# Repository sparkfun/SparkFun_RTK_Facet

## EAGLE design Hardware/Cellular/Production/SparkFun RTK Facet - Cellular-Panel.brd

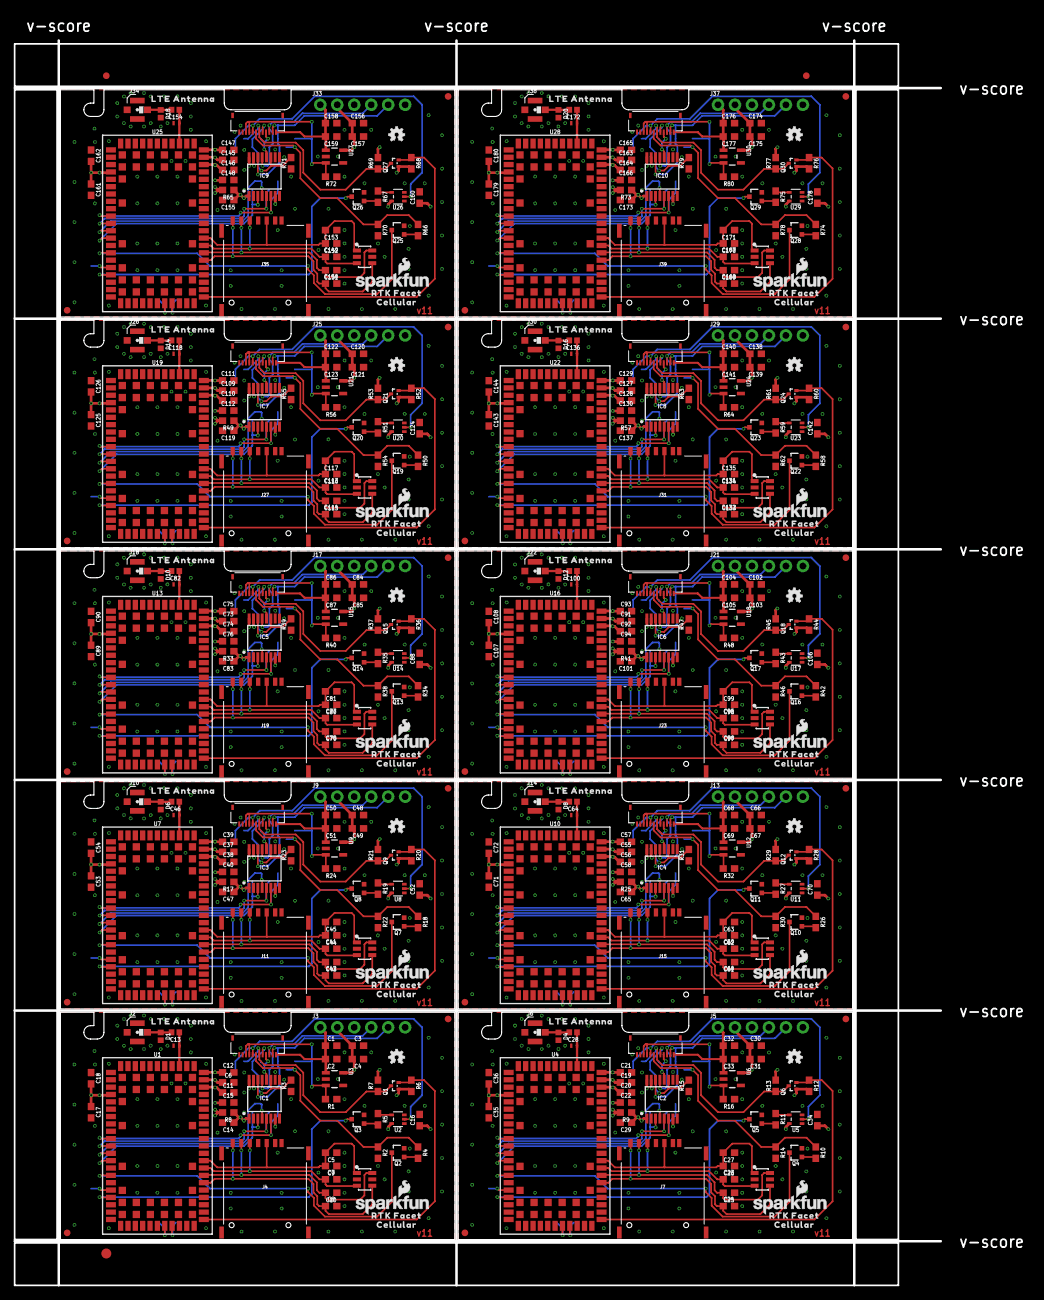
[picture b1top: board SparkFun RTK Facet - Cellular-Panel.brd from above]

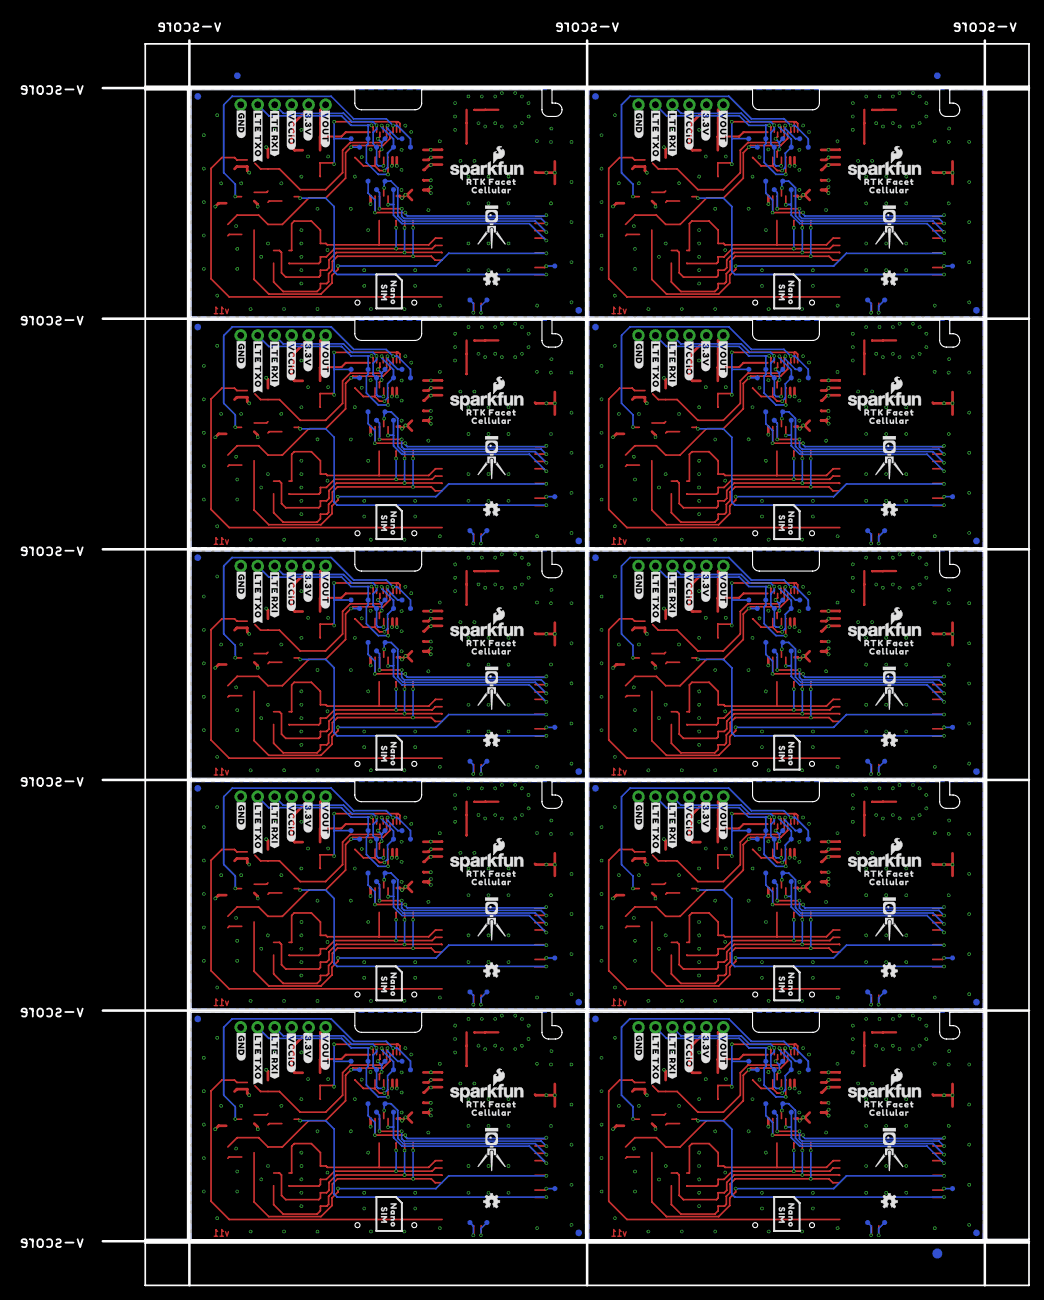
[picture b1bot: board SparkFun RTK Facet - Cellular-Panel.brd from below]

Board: 4 copper layers, 138.6 x 186.3 mm, 776 parts (303 on the bottom side), 320 nets.

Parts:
C1, C3, C17, C30, C32, C35, C48, C50, C53, C66, C68, C71, C84, C86, C89, C102, C104, C107, C120, C122, C125, C138, C140, C143, C156, C158, C161, C174, C176, C179: 1.0uF; 0603
C2, C4, C5, C6, C14, C16, C18, C19, C27, C29, C31, C33, C34, C36, C37, C45, C47, C49, C51, C52, C54, C55, C63, C65, C67, C69, C70, C72, C73, C81, C83, C85, C87, C88, C90, C91, C99, C101, C103, C105, C106, C108, C109, C117, C119, C121, C123, C124, C126, C127, C135, C137, C139, C141, C142, C144, C145, C153, C155, C157, C159, C160, C162, C163, C171, C173, C175, C177, C178, C180: 0.1uF; 0603
C7, C8, C9, C10, C23, C24, C25, C26, C41, C42, C43, C44, C59, C60, C61, C62, C77, C78, C79, C80, C95, C96, C97, C98, C113, C114, C115, C116, C131, C132, C133, C134, C149, C150, C151, C152, C167, C168, C169, C170: 47pF; 0603
C11, C20, C38, C56, C74, C92, C110, C128, C146, C164: 68pF; 0603
C12, C21, C39, C57, C75, C93, C111, C129, C147, C165: 10uF; 0603
C13, C28, C46, C64, C82, C100, C118, C136, C154, C172: 33pF; 0402
C15, C22, C40, C58, C76, C94, C112, C130, C148, C166: 15pF; 0603
D1, D4, D6, D8, D10, D12, D14, D16, D18, D20: PESD0402; 0402
D2, D3, D5, D7, D9, D11, D13, D15, D17, D19: DT1042-04SO-7; SOT23-6L
E$1, E$2, E$3, E$4: FIDUCIAL-1X2
E$5, E$6: FIDUCIAL-1.5X3
FID1, FID2, FID3, FID4, FID5, FID6, FID7, FID8, FID9, FID10, FID11, FID12, FID13, FID14, FID15, FID16, FID17, FID18, FID19, FID20, FID21, FID22, FID23, FID24, FID25, FID26, FID27, FID28, FID29, FID30, FID31, FID32, FID33, FID34, FID35, FID36, FID37, FID38, FID39, FID40: FIDUCIAL1X2; FIDUCIAL-1X2
IC1, IC2, IC3, IC4, IC5, IC6, IC7, IC8, IC9, IC10: SN74AVC4T774PW; SOP65P640X120-16N
J1, J8, J12, J16, J20, J24, J28, J32, J36, J40: FPC_12_DOUBLESIDED_BACKFLIP
J2, J6, J10, J14, J18, J22, J26, J30, J34, J38: U.FL
J3, J5, J9, J13, J17, J21, J25, J29, J33, J37: DIAG; 1X06_NO_SILK
J4, J7, J11, J15, J19, J23, J27, J31, J35, J39: NANO_SIM_PP_REDUCED_PADS
L1, L2, L3, L4, L5, L6, L7, L8, L9, L10: DNP; 0402_COILCRAFT
LOGO1, LOGO3, LOGO4, LOGO8, LOGO9, LOGO12, LOGO13, LOGO16, LOGO17, LOGO20, LOGO21, LOGO24, LOGO25, LOGO28, LOGO29, LOGO32, LOGO33, LOGO36, LOGO37, LOGO40: OSHW-LOGOMINI; OSHW-LOGO-MINI
LOGO2, LOGO5, LOGO6, LOGO7, LOGO10, LOGO11, LOGO14, LOGO15, LOGO18, LOGO19, LOGO22, LOGO23, LOGO26, LOGO27, LOGO30, LOGO31, LOGO34, LOGO35, LOGO38, LOGO39: SFE_LOGO_NAME_FLAME.1_INCH; SFE_LOGO_NAME_FLAME_.1
Q1, Q6, Q9, Q12, Q15, Q18, Q21, Q24, Q27, Q30: 20V/0.2A/8MHz/1.2Ω/1Vth; SOT-416FL
Q2, Q3, Q4, Q5, Q7, Q8, Q10, Q11, Q13, Q14, Q16, Q17, Q19, Q20, Q22, Q23, Q25, Q26, Q28, Q29: 310mA/60V/1.6Ω; SOT323
R1, R2, R3, R14, R15, R16, R22, R23, R24, R30, R31, R32, R38, R39, R40, R46, R47, R48, R54, R55, R56, R62, R63, R64, R70, R71, R72, R78, R79, R80: 100k; 0603
R4, R5, R10, R11, R18, R19, R26, R27, R34, R35, R42, R43, R50, R51, R58, R59, R66, R67, R74, R75: 1k; 0603
R6, R7, R12, R13, R20, R21, R28, R29, R36, R37, R44, R45, R52, R53, R60, R61, R68, R69, R76, R77: 2.2k; 0603
R8, R9, R17, R25, R33, R41, R49, R57, R65, R73: 0; 0603
TP1, TP2, TP3, TP4, TP5, TP6, TP7, TP8, TP9, TP10, TP11, TP12, TP13, TP14, TP15, TP16, TP17, TP18, TP19, TP20, TP21, TP22, TP23, TP24, TP25, TP26, TP27, TP28, TP29, TP30, TP31, TP32, TP33, TP34, TP35, TP36, TP37, TP38, TP39, TP40, TP41, TP42, TP43, TP44, TP45, TP46, TP47, TP48, TP49, TP50, TP51, TP52, TP53, TP54, TP55, TP56, TP57, TP58, TP59, TP60, TP61, TP62, TP63, TP64, TP65, TP66, TP67, TP68, TP69, TP70, TP71, TP72, TP73, TP74, TP75, TP76, TP77, TP78, TP79, TP80, TP81, TP82, TP83, TP84, TP85, TP86, TP87, TP88, TP89, TP90, TP91, TP92, TP93, TP94, TP95, TP96, TP97, TP98, TP99, TP100, TP101, TP102, TP103, TP104, TP105, TP106, TP107, TP108, TP109, TP110, TP111, TP112, TP113, TP114, TP115, TP116, TP117, TP118, TP119, TP120, TP121, TP122, TP123, TP124, TP125, TP126, TP127, TP128, TP129, TP130, TP131, TP132, TP133, TP134, TP135, TP136, TP137, TP138, TP139, TP140, TP141, TP142, TP143, TP144, TP145, TP146, TP147, TP148, TP149, TP150: TEST-POINT3; PAD.03X.03
U1, U4, U7, U10, U13, U16, U19, U22, U25, U28: SARA-R510M8S; SARA-LGA
U2, U5, U8, U11, U14, U17, U20, U23, U26, U29: 74HC1G04; SOT353
U3, U6, U9, U12, U15, U18, U21, U24, U27, U30: AP2112K-3.3; SOT23-5
U$1, U$12, U$14, U$17, U$28, U$31, U$42, U$45, U$56, U$59, U$70, U$73, U$84, U$87, U$98, U$101, U$112, U$115, U$126, U$129: RTK_FACET0
U$2, U$3, U$11, U$18, U$27, U$32, U$41, U$46, U$55, U$60, U$69, U$74, U$83, U$88, U$97, U$102, U$111, U$116, U$125, U$132: CELLULAR1
U$4, U$19, U$33, U$47, U$61, U$75, U$89, U$103, U$117, U$133: #VOUT#0
U$5, U$20, U$34, U$48, U$62, U$76, U$90, U$104, U$118, U$134: #3#3V#0
U$6, U$21, U$35, U$49, U$63, U$77, U$91, U$105, U$119, U$135: #VCCIO#0
U$7, U$22, U$36, U$50, U$64, U$78, U$92, U$106, U$120, U$136: #LTE_RXI#0
U$8, U$23, U$37, U$51, U$65, U$79, U$93, U$107, U$121, U$137: #LTE_TXO#0
U$9, U$24, U$38, U$52, U$66, U$80, U$94, U$108, U$122, U$138: #GND#0
U$10, U$26, U$40, U$54, U$68, U$82, U$96, U$110, U$124, U$140: LTE_ANTENNA0
U$13, U$29, U$43, U$57, U$71, U$85, U$99, U$113, U$127, U$130: NANO0
U$15, U$25, U$39, U$53, U$67, U$81, U$95, U$109, U$123, U$139: RTK5#SVG0
U$16, U$30, U$44, U$58, U$72, U$86, U$100, U$114, U$128, U$131: SIM0

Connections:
3.3V: C3.1, C4.2, C6.1, C11.1, C12.1, C15.1, C16.1, IC1.15, J3.2, R7.2, U1.51, U1.52, U1.53, U2.5, U3.5
3.3V1: C19.1, C20.1, C21.1, C22.1, C30.1, C31.2, C34.1, IC2.15, J5.2, R13.2, U4.51, U4.52, U4.53, U5.5, U6.5
3.3V2: C37.1, C38.1, C39.1, C40.1, C48.1, C49.2, C52.1, IC3.15, J9.2, R21.2, U7.51, U7.52, U7.53, U8.5, U9.5
3.3V3: C55.1, C56.1, C57.1, C58.1, C66.1, C67.2, C70.1, IC4.15, J13.2, R29.2, U10.51, U10.52, U10.53, U11.5, U12.5
3.3V4: C73.1, C74.1, C75.1, C76.1, C84.1, C85.2, C88.1, IC5.15, J17.2, R37.2, U13.51, U13.52, U13.53, U14.5, U15.5
3.3V5: C91.1, C92.1, C93.1, C94.1, C102.1, C103.2, C106.1, IC6.15, J21.2, R45.2, U16.51, U16.52, U16.53, U17.5, U18.5
3.3V6: C109.1, C110.1, C111.1, C112.1, C120.1, C121.2, C124.1, IC7.15, J25.2, R53.2, U19.51, U19.52, U19.53, U20.5, U21.5
3.3V7: C127.1, C128.1, C129.1, C130.1, C138.1, C139.2, C142.1, IC8.15, J29.2, R61.2, U22.51, U22.52, U22.53, U23.5, U24.5
3.3V8: C145.1, C146.1, C147.1, C148.1, C156.1, C157.2, C160.1, IC9.15, J33.2, R69.2, U25.51, U25.52, U25.53, U26.5, U27.5
3.3V9: C163.1, C164.1, C165.1, C166.1, C174.1, C175.2, C178.1, IC10.15, J37.2, R77.2, U28.51, U28.52, U28.53, U29.5, U30.5
GND: C1.2, C2.1, C3.2, C4.1, C5.1, C6.2, C7.2, C8.2, C9.1, C10.1, C11.2, C12.2, C14.2, C15.2, C16.2, C17.2, C18.1, D1.2, D2.2, D2.5, IC1.2, IC1.8, IC1.9, IC1.10, J1.11, J1.12, J2.1, J2.2, J3.6, J4.C5, L1.P$2, Q2.2, Q3.2, R1.1, R2.2, R3.1, U1.1, U1.3, U1.5, U1.9, U1.14, U1.20, U1.21, U1.22, U1.30, U1.32, U1.43, U1.50, U1.54, U1.55, U1.57, U1.58, U1.59, U1.60, U1.61, U1.63, U1.64, U1.65, U1.66, U1.67, U1.68, U1.69, U1.70, U1.71, U1.72, U1.73, U1.74, U1.75, U1.76, U1.77, U1.78, U1.79, U1.80, U1.81, U1.82, U1.83, U1.84, U1.85, U1.86, U1.87, U1.88, U1.89, U1.90, U1.91, U1.92, U1.93, U1.94, U1.95, U1.96, U2.3, U3.2
GND1: C19.2, C20.2, C21.2, C22.2, C23.2, C24.2, C25.1, C26.1, C27.1, C29.2, C30.2, C31.1, C32.2, C33.1, C34.2, C35.2, C36.1, D3.2, D3.5, D4.2, IC2.2, IC2.8, IC2.9, IC2.10, J5.6, J6.1, J6.2, J7.C5, J8.11, J8.12, L2.P$2, Q4.2, Q5.2, R14.2, R15.1, R16.1, U4.1, U4.3, U4.5, U4.9, U4.14, U4.20, U4.21, U4.22, U4.30, U4.32, U4.43, U4.50, U4.54, U4.55, U4.57, U4.58, U4.59, U4.60, U4.61, U4.63, U4.64, U4.65, U4.66, U4.67, U4.68, U4.69, U4.70, U4.71, U4.72, U4.73, U4.74, U4.75, U4.76, U4.77, U4.78, U4.79, U4.80, U4.81, U4.82, U4.83, U4.84, U4.85, U4.86, U4.87, U4.88, U4.89, U4.90, U4.91, U4.92, U4.93, U4.94, U4.95, U4.96, U5.3, U6.2
GND2: C37.2, C38.2, C39.2, C40.2, C41.2, C42.2, C43.1, C44.1, C45.1, C47.2, C48.2, C49.1, C50.2, C51.1, C52.2, C53.2, C54.1, D5.2, D5.5, D6.2, IC3.2, IC3.8, IC3.9, IC3.10, J9.6, J10.1, J10.2, J11.C5, J12.11, J12.12, L3.P$2, Q7.2, Q8.2, R22.2, R23.1, R24.1, U7.1, U7.3, U7.5, U7.9, U7.14, U7.20, U7.21, U7.22, U7.30, U7.32, U7.43, U7.50, U7.54, U7.55, U7.57, U7.58, U7.59, U7.60, U7.61, U7.63, U7.64, U7.65, U7.66, U7.67, U7.68, U7.69, U7.70, U7.71, U7.72, U7.73, U7.74, U7.75, U7.76, U7.77, U7.78, U7.79, U7.80, U7.81, U7.82, U7.83, U7.84, U7.85, U7.86, U7.87, U7.88, U7.89, U7.90, U7.91, U7.92, U7.93, U7.94, U7.95, U7.96, U8.3, U9.2
GND3: C55.2, C56.2, C57.2, C58.2, C59.2, C60.2, C61.1, C62.1, C63.1, C65.2, C66.2, C67.1, C68.2, C69.1, C70.2, C71.2, C72.1, D7.2, D7.5, D8.2, IC4.2, IC4.8, IC4.9, IC4.10, J13.6, J14.1, J14.2, J15.C5, J16.11, J16.12, L4.P$2, Q10.2, Q11.2, R30.2, R31.1, R32.1, U10.1, U10.3, U10.5, U10.9, U10.14, U10.20, U10.21, U10.22, U10.30, U10.32, U10.43, U10.50, U10.54, U10.55, U10.57, U10.58, U10.59, U10.60, U10.61, U10.63, U10.64, U10.65, U10.66, U10.67, U10.68, U10.69, U10.70, U10.71, U10.72, U10.73, U10.74, U10.75, U10.76, U10.77, U10.78, U10.79, U10.80, U10.81, U10.82, U10.83, U10.84, U10.85, U10.86, U10.87, U10.88, U10.89, U10.90, U10.91, U10.92, U10.93, U10.94, U10.95, U10.96, U11.3, U12.2
GND4: C73.2, C74.2, C75.2, C76.2, C77.2, C78.2, C79.1, C80.1, C81.1, C83.2, C84.2, C85.1, C86.2, C87.1, C88.2, C89.2, C90.1, D9.2, D9.5, D10.2, IC5.2, IC5.8, IC5.9, IC5.10, J17.6, J18.1, J18.2, J19.C5, J20.11, J20.12, L5.P$2, Q13.2, Q14.2, R38.2, R39.1, R40.1, U13.1, U13.3, U13.5, U13.9, U13.14, U13.20, U13.21, U13.22, U13.30, U13.32, U13.43, U13.50, U13.54, U13.55, U13.57, U13.58, U13.59, U13.60, U13.61, U13.63, U13.64, U13.65, U13.66, U13.67, U13.68, U13.69, U13.70, U13.71, U13.72, U13.73, U13.74, U13.75, U13.76, U13.77, U13.78, U13.79, U13.80, U13.81, U13.82, U13.83, U13.84, U13.85, U13.86, U13.87, U13.88, U13.89, U13.90, U13.91, U13.92, U13.93, U13.94, U13.95, U13.96, U14.3, U15.2
GND5: C91.2, C92.2, C93.2, C94.2, C95.2, C96.2, C97.1, C98.1, C99.1, C101.2, C102.2, C103.1, C104.2, C105.1, C106.2, C107.2, C108.1, D11.2, D11.5, D12.2, IC6.2, IC6.8, IC6.9, IC6.10, J21.6, J22.1, J22.2, J23.C5, J24.11, J24.12, L6.P$2, Q16.2, Q17.2, R46.2, R47.1, R48.1, U16.1, U16.3, U16.5, U16.9, U16.14, U16.20, U16.21, U16.22, U16.30, U16.32, U16.43, U16.50, U16.54, U16.55, U16.57, U16.58, U16.59, U16.60, U16.61, U16.63, U16.64, U16.65, U16.66, U16.67, U16.68, U16.69, U16.70, U16.71, U16.72, U16.73, U16.74, U16.75, U16.76, U16.77, U16.78, U16.79, U16.80, U16.81, U16.82, U16.83, U16.84, U16.85, U16.86, U16.87, U16.88, U16.89, U16.90, U16.91, U16.92, U16.93, U16.94, U16.95, U16.96, U17.3, U18.2
GND6: C109.2, C110.2, C111.2, C112.2, C113.2, C114.2, C115.1, C116.1, C117.1, C119.2, C120.2, C121.1, C122.2, C123.1, C124.2, C125.2, C126.1, D13.2, D13.5, D14.2, IC7.2, IC7.8, IC7.9, IC7.10, J25.6, J26.1, J26.2, J27.C5, J28.11, J28.12, L7.P$2, Q19.2, Q20.2, R54.2, R55.1, R56.1, U19.1, U19.3, U19.5, U19.9, U19.14, U19.20, U19.21, U19.22, U19.30, U19.32, U19.43, U19.50, U19.54, U19.55, U19.57, U19.58, U19.59, U19.60, U19.61, U19.63, U19.64, U19.65, U19.66, U19.67, U19.68, U19.69, U19.70, U19.71, U19.72, U19.73, U19.74, U19.75, U19.76, U19.77, U19.78, U19.79, U19.80, U19.81, U19.82, U19.83, U19.84, U19.85, U19.86, U19.87, U19.88, U19.89, U19.90, U19.91, U19.92, U19.93, U19.94, U19.95, U19.96, U20.3, U21.2
GND7: C127.2, C128.2, C129.2, C130.2, C131.2, C132.2, C133.1, C134.1, C135.1, C137.2, C138.2, C139.1, C140.2, C141.1, C142.2, C143.2, C144.1, D15.2, D15.5, D16.2, IC8.2, IC8.8, IC8.9, IC8.10, J29.6, J30.1, J30.2, J31.C5, J32.11, J32.12, L8.P$2, Q22.2, Q23.2, R62.2, R63.1, R64.1, U22.1, U22.3, U22.5, U22.9, U22.14, U22.20, U22.21, U22.22, U22.30, U22.32, U22.43, U22.50, U22.54, U22.55, U22.57, U22.58, U22.59, U22.60, U22.61, U22.63, U22.64, U22.65, U22.66, U22.67, U22.68, U22.69, U22.70, U22.71, U22.72, U22.73, U22.74, U22.75, U22.76, U22.77, U22.78, U22.79, U22.80, U22.81, U22.82, U22.83, U22.84, U22.85, U22.86, U22.87, U22.88, U22.89, U22.90, U22.91, U22.92, U22.93, U22.94, U22.95, U22.96, U23.3, U24.2
GND8: C145.2, C146.2, C147.2, C148.2, C149.2, C150.2, C151.1, C152.1, C153.1, C155.2, C156.2, C157.1, C158.2, C159.1, C160.2, C161.2, C162.1, D17.2, D17.5, D18.2, IC9.2, IC9.8, IC9.9, IC9.10, J33.6, J34.1, J34.2, J35.C5, J36.11, J36.12, L9.P$2, Q25.2, Q26.2, R70.2, R71.1, R72.1, U25.1, U25.3, U25.5, U25.9, U25.14, U25.20, U25.21, U25.22, U25.30, U25.32, U25.43, U25.50, U25.54, U25.55, U25.57, U25.58, U25.59, U25.60, U25.61, U25.63, U25.64, U25.65, U25.66, U25.67, U25.68, U25.69, U25.70, U25.71, U25.72, U25.73, U25.74, U25.75, U25.76, U25.77, U25.78, U25.79, U25.80, U25.81, U25.82, U25.83, U25.84, U25.85, U25.86, U25.87, U25.88, U25.89, U25.90, U25.91, U25.92, U25.93, U25.94, U25.95, U25.96, U26.3, U27.2
GND9: C163.2, C164.2, C165.2, C166.2, C167.2, C168.2, C169.1, C170.1, C171.1, C173.2, C174.2, C175.1, C176.2, C177.1, C178.2, C179.2, C180.1, D19.2, D19.5, D20.2, IC10.2, IC10.8, IC10.9, IC10.10, J37.6, J38.1, J38.2, J39.C5, J40.11, J40.12, L10.P$2, Q28.2, Q29.2, R78.2, R79.1, R80.1, U28.1, U28.3, U28.5, U28.9, U28.14, U28.20, U28.21, U28.22, U28.30, U28.32, U28.43, U28.50, U28.54, U28.55, U28.57, U28.58, U28.59, U28.60, U28.61, U28.63, U28.64, U28.65, U28.66, U28.67, U28.68, U28.69, U28.70, U28.71, U28.72, U28.73, U28.74, U28.75, U28.76, U28.77, U28.78, U28.79, U28.80, U28.81, U28.82, U28.83, U28.84, U28.85, U28.86, U28.87, U28.88, U28.89, U28.90, U28.91, U28.92, U28.93, U28.94, U28.95, U28.96, U29.3, U30.2
LTE_!RESET!: J1.8, TP14.1, U2.2
LTE_!RESET!1: J8.8, TP29.1, U5.2
LTE_!RESET!2: J12.8, TP44.1, U8.2
LTE_!RESET!3: J16.8, TP59.1, U11.2
LTE_!RESET!4: J20.8, TP74.1, U14.2
LTE_!RESET!5: J24.8, TP89.1, U17.2
LTE_!RESET!6: J28.8, TP104.1, U20.2
LTE_!RESET!7: J32.8, TP119.1, U23.2
LTE_!RESET!8: J36.8, TP134.1, U26.2
LTE_!RESET!9: J40.8, TP149.1, U29.2
LTE_CTSI: IC1.11, J1.5, R3.2, TP8.1
LTE_CTSI1: IC2.11, J8.5, R15.2, TP23.1
LTE_CTSI2: IC3.11, J12.5, R23.2, TP38.1
LTE_CTSI3: IC4.11, J16.5, R31.2, TP53.1
LTE_CTSI4: IC5.11, J20.5, R39.2, TP68.1
LTE_CTSI5: IC6.11, J24.5, R47.2, TP83.1
LTE_CTSI6: IC7.11, J28.5, R55.2, TP98.1
LTE_CTSI7: IC8.11, J32.5, R63.2, TP113.1
LTE_CTSI8: IC9.11, J36.5, R71.2, TP128.1
LTE_CTSI9: IC10.11, J40.5, R79.2, TP143.1
LTE_INT: J1.6, Q1.3, R7.1, TP12.1
LTE_INT1: J8.6, Q6.3, R13.1, TP24.1
LTE_INT2: J12.6, Q9.3, R21.1, TP39.1
LTE_INT3: J16.6, Q12.3, R29.1, TP54.1
LTE_INT4: J20.6, Q15.3, R37.1, TP69.1
LTE_INT5: J24.6, Q18.3, R45.1, TP84.1
LTE_INT6: J28.6, Q21.3, R53.1, TP99.1
LTE_INT7: J32.6, Q24.3, R61.1, TP114.1
LTE_INT8: J36.6, Q27.3, R69.1, TP129.1
LTE_INT9: J40.6, Q30.3, R77.1, TP144.1
LTE_PWR_ON: J1.7, R2.1, R4.1, TP13.1
LTE_PWR_ON1: J8.7, R10.1, R14.1, TP28.1
LTE_PWR_ON2: J12.7, R18.1, R22.1, TP43.1
LTE_PWR_ON3: J16.7, R26.1, R30.1, TP58.1
LTE_PWR_ON4: J20.7, R34.1, R38.1, TP73.1
LTE_PWR_ON5: J24.7, R42.1, R46.1, TP88.1
LTE_PWR_ON6: J28.7, R50.1, R54.1, TP103.1
LTE_PWR_ON7: J32.7, R58.1, R62.1, TP118.1
LTE_PWR_ON8: J36.7, R66.1, R70.1, TP133.1
LTE_PWR_ON9: J40.7, R74.1, R78.1, TP148.1
LTE_RTSO: IC1.12, J1.4, TP7.1
LTE_RTSO1: IC2.12, J8.4, TP22.1
LTE_RTSO2: IC3.12, J12.4, TP37.1
LTE_RTSO3: IC4.12, J16.4, TP52.1
LTE_RTSO4: IC5.12, J20.4, TP67.1
LTE_RTSO5: IC6.12, J24.4, TP82.1
LTE_RTSO6: IC7.12, J28.4, TP97.1
LTE_RTSO7: IC8.12, J32.4, TP112.1
LTE_RTSO8: IC9.12, J36.4, TP127.1
LTE_RTSO9: IC10.12, J40.4, TP142.1
LTE_RXI: IC1.13, J1.3, J3.4, TP6.1
LTE_RXI1: IC2.13, J5.4, J8.3, TP21.1
LTE_RXI2: IC3.13, J9.4, J12.3, TP36.1
LTE_RXI3: IC4.13, J13.4, J16.3, TP51.1
LTE_RXI4: IC5.13, J17.4, J20.3, TP66.1
LTE_RXI5: IC6.13, J21.4, J24.3, TP81.1
LTE_RXI6: IC7.13, J25.4, J28.3, TP96.1
LTE_RXI7: IC8.13, J29.4, J32.3, TP111.1
LTE_RXI8: IC9.13, J33.4, J36.3, TP126.1
LTE_RXI9: IC10.13, J37.4, J40.3, TP141.1
LTE_TXO: IC1.14, J1.2, J3.5, TP5.1
LTE_TXO1: IC2.14, J5.5, J8.2, TP20.1
LTE_TXO2: IC3.14, J9.5, J12.2, TP35.1
LTE_TXO3: IC4.14, J13.5, J16.2, TP50.1
LTE_TXO4: IC5.14, J17.5, J20.2, TP65.1
LTE_TXO5: IC6.14, J21.5, J24.2, TP80.1
LTE_TXO6: IC7.14, J25.5, J28.2, TP95.1
LTE_TXO7: IC8.14, J29.5, J32.2, TP110.1
LTE_TXO8: IC9.14, J33.5, J36.2, TP125.1
LTE_TXO9: IC10.14, J37.5, J40.2, TP140.1
MAIN_3V1: J8.9, J8.10, R16.2, TP30.1, U6.3
MAIN_3V2: J12.9, J12.10, R24.2, TP45.1, U9.3
MAIN_3V3: J1.9, J1.10, R1.2, TP15.1, U3.3
MAIN_3V4: J16.9, J16.10, R32.2, TP60.1, U12.3
MAIN_3V5: J20.9, J20.10, R40.2, TP75.1, U15.3
MAIN_3V6: J24.9, J24.10, R48.2, TP90.1, U18.3
MAIN_3V7: J28.9, J28.10, R56.2, TP105.1, U21.3
MAIN_3V8: J32.9, J32.10, R64.2, TP120.1, U24.3
MAIN_3V9: J36.9, J36.10, R72.2, TP135.1, U27.3
MAIN_3V10: J40.9, J40.10, R80.2, TP150.1, U30.3
unnamed: TP9.1, U1.28
unnamed: TP10.1, U1.29
unnamed: TP11.1, U1.17
unnamed: C35.1, C36.2, R9.2, U4.4
unnamed: C28.2, D4.1, J6.FEED
unnamed: Q4.1, R10.2
unnamed: Q5.1, R11.2
unnamed: R11.1, U5.4
unnamed: TP25.1, U4.28
unnamed: TP26.1, U4.29
unnamed: TP27.1, U4.17
unnamed: C53.1, C54.2, R17.2, U7.4
unnamed: C46.2, D6.1, J10.FEED
unnamed: Q7.1, R18.2
unnamed: C13.2, D1.1, J2.FEED
unnamed: Q8.1, R19.2
unnamed: R19.1, U8.4
unnamed: TP40.1, U7.28
unnamed: TP41.1, U7.29
unnamed: TP42.1, U7.17
unnamed: C71.1, C72.2, R25.2, U10.4
unnamed: C64.2, D8.1, J14.FEED
unnamed: Q10.1, R26.2
unnamed: Q11.1, R27.2
unnamed: R27.1, U11.4
unnamed: Q2.1, R4.2
unnamed: Q3.1, R5.2
unnamed: R5.1, U2.4
unnamed: TP55.1, U10.28
unnamed: TP56.1, U10.29
unnamed: C17.1, C18.2, R8.2, U1.4
unnamed: TP57.1, U10.17
unnamed: C89.1, C90.2, R33.2, U13.4
unnamed: C82.2, D10.1, J18.FEED
unnamed: Q13.1, R34.2
unnamed: Q14.1, R35.2
unnamed: R35.1, U14.4
unnamed: TP70.1, U13.28
unnamed: TP71.1, U13.29
unnamed: TP72.1, U13.17
unnamed: C107.1, C108.2, R41.2, U16.4
unnamed: C100.2, D12.1, J22.FEED
unnamed: Q16.1, R42.2
unnamed: Q17.1, R43.2
unnamed: R43.1, U17.4
unnamed: TP85.1, U16.28
unnamed: TP86.1, U16.29
unnamed: TP87.1, U16.17
unnamed: C125.1, C126.2, R49.2, U19.4
unnamed: C118.2, D14.1, J26.FEED
unnamed: Q19.1, R50.2
unnamed: Q20.1, R51.2
unnamed: R51.1, U20.4
unnamed: TP100.1, U19.28
unnamed: TP101.1, U19.29
unnamed: TP102.1, U19.17
unnamed: C143.1, C144.2, R57.2, U22.4
unnamed: C136.2, D16.1, J30.FEED
unnamed: Q22.1, R58.2
unnamed: Q23.1, R59.2
unnamed: R59.1, U23.4
unnamed: TP115.1, U22.28
unnamed: TP116.1, U22.29
unnamed: TP117.1, U22.17
unnamed: C161.1, C162.2, R65.2, U25.4
unnamed: C154.2, D18.1, J34.FEED
unnamed: Q25.1, R66.2
unnamed: Q26.1, R67.2
unnamed: R67.1, U26.4
unnamed: TP130.1, U25.28
unnamed: TP131.1, U25.29
unnamed: TP132.1, U25.17
unnamed: C179.1, C180.2, R73.2, U28.4
unnamed: C172.2, D20.1, J38.FEED
unnamed: Q28.1, R74.2
unnamed: Q29.1, R75.2
unnamed: R75.1, U29.4
unnamed: TP145.1, U28.28
unnamed: TP146.1, U28.29
unnamed: TP147.1, U28.17
SARA_!RESET!: Q3.3, U1.18
SARA_!RESET!1: Q5.3, U4.18
SARA_!RESET!2: Q8.3, U7.18
SARA_!RESET!3: Q11.3, U10.18
SARA_!RESET!4: Q14.3, U13.18
SARA_!RESET!5: Q17.3, U16.18
SARA_!RESET!6: Q20.3, U19.18
SARA_!RESET!7: Q23.3, U22.18
SARA_!RESET!8: Q26.3, U25.18
SARA_!RESET!9: Q29.3, U28.18
SARA_ANT: C13.1, L1.P$1, U1.56
SARA_ANT1: C28.1, L2.P$1, U4.56
SARA_ANT2: C46.1, L3.P$1, U7.56
SARA_ANT3: C64.1, L4.P$1, U10.56
SARA_ANT4: C82.1, L5.P$1, U13.56
SARA_ANT5: C100.1, L6.P$1, U16.56
SARA_ANT6: C118.1, L7.P$1, U19.56
SARA_ANT7: C136.1, L8.P$1, U22.56
SARA_ANT8: C154.1, L9.P$1, U25.56
SARA_ANT9: C172.1, L10.P$1, U28.56
SARA_CTSO: IC1.5, TP3.1, U1.11
SARA_CTSO1: IC2.5, TP18.1, U4.11
SARA_CTSO2: IC3.5, TP33.1, U7.11
SARA_CTSO3: IC4.5, TP48.1, U10.11
SARA_CTSO4: IC5.5, TP63.1, U13.11
SARA_CTSO5: IC6.5, TP78.1, U16.11
SARA_CTSO6: IC7.5, TP93.1, U19.11
SARA_CTSO7: IC8.5, TP108.1, U22.11
SARA_CTSO8: IC9.5, TP123.1, U25.11
SARA_CTSO9: IC10.5, TP138.1, U28.11
SARA_EXT_INT: Q1.2, R6.1, U1.33
SARA_EXT_INT1: Q6.2, R12.1, U4.33
SARA_EXT_INT2: Q9.2, R20.1, U7.33
SARA_EXT_INT3: Q12.2, R28.1, U10.33
SARA_EXT_INT4: Q15.2, R36.1, U13.33
SARA_EXT_INT5: Q18.2, R44.1, U16.33
SARA_EXT_INT6: Q21.2, R52.1, U19.33
SARA_EXT_INT7: Q24.2, R60.1, U22.33
SARA_EXT_INT8: Q27.2, R68.1, U25.33
SARA_EXT_INT9: Q30.2, R76.1, U28.33
SARA_PWR_ON: Q2.3, U1.15
SARA_PWR_ON1: Q4.3, U4.15
SARA_PWR_ON2: Q7.3, U7.15
SARA_PWR_ON3: Q10.3, U10.15
SARA_PWR_ON4: Q13.3, U13.15
SARA_PWR_ON5: Q16.3, U16.15
SARA_PWR_ON6: Q19.3, U19.15
SARA_PWR_ON7: Q22.3, U22.15
SARA_PWR_ON8: Q25.3, U25.15
SARA_PWR_ON9: Q28.3, U28.15
SARA_RTSI: IC1.6, TP4.1, U1.10
SARA_RTSI1: IC2.6, TP19.1, U4.10
SARA_RTSI2: IC3.6, TP34.1, U7.10
SARA_RTSI3: IC4.6, TP49.1, U10.10
SARA_RTSI4: IC5.6, TP64.1, U13.10
SARA_RTSI5: IC6.6, TP79.1, U16.10
SARA_RTSI6: IC7.6, TP94.1, U19.10
SARA_RTSI7: IC8.6, TP109.1, U22.10
SARA_RTSI8: IC9.6, TP124.1, U25.10
SARA_RTSI9: IC10.6, TP139.1, U28.10
SARA_RXO: IC1.3, TP1.1, U1.13
SARA_RXO1: IC2.3, TP16.1, U4.13
SARA_RXO2: IC3.3, TP31.1, U7.13
SARA_RXO3: IC4.3, TP46.1, U10.13
SARA_RXO4: IC5.3, TP61.1, U13.13
SARA_RXO5: IC6.3, TP76.1, U16.13
SARA_RXO6: IC7.3, TP91.1, U19.13
SARA_RXO7: IC8.3, TP106.1, U22.13
SARA_RXO8: IC9.3, TP121.1, U25.13
SARA_RXO9: IC10.3, TP136.1, U28.13
SARA_TXI: IC1.4, TP2.1, U1.12
SARA_TXI1: IC2.4, TP17.1, U4.12
SARA_TXI2: IC3.4, TP32.1, U7.12
SARA_TXI3: IC4.4, TP47.1, U10.12
SARA_TXI4: IC5.4, TP62.1, U13.12
SARA_TXI5: IC6.4, TP77.1, U16.12
SARA_TXI6: IC7.4, TP92.1, U19.12
SARA_TXI7: IC8.4, TP107.1, U22.12
SARA_TXI8: IC9.4, TP122.1, U25.12
SARA_TXI9: IC10.4, TP137.1, U28.12
SIM_CLK: C8.1, D2.4, J4.C3, U1.38
SIM_CLK1: C24.1, D3.4, J7.C3, U4.38
SIM_CLK2: C42.1, D5.4, J11.C3, U7.38
SIM_CLK3: C60.1, D7.4, J15.C3, U10.38
SIM_CLK4: C78.1, D9.4, J19.C3, U13.38
SIM_CLK5: C96.1, D11.4, J23.C3, U16.38
SIM_CLK6: C114.1, D13.4, J27.C3, U19.38
SIM_CLK7: C132.1, D15.4, J31.C3, U22.38
SIM_CLK8: C150.1, D17.4, J35.C3, U25.38
SIM_CLK9: C168.1, D19.4, J39.C3, U28.38
SIM_IO: C10.2, D2.6, J4.C7, U1.39
SIM_IO1: C25.2, D3.6, J7.C7, U4.39
SIM_IO2: C43.2, D5.6, J11.C7, U7.39
SIM_IO3: C61.2, D7.6, J15.C7, U10.39
SIM_IO4: C79.2, D9.6, J19.C7, U13.39
SIM_IO5: C97.2, D11.6, J23.C7, U16.39
SIM_IO6: C115.2, D13.6, J27.C7, U19.39
SIM_IO7: C133.2, D15.6, J31.C7, U22.39
SIM_IO8: C151.2, D17.6, J35.C7, U25.39
SIM_IO9: C169.2, D19.6, J39.C7, U28.39
SIM_RST: C7.1, D2.3, J4.C2, U1.40
SIM_RST1: C23.1, D3.3, J7.C2, U4.40
SIM_RST2: C41.1, D5.3, J11.C2, U7.40
SIM_RST3: C59.1, D7.3, J15.C2, U10.40
SIM_RST4: C77.1, D9.3, J19.C2, U13.40
SIM_RST5: C95.1, D11.3, J23.C2, U16.40
SIM_RST6: C113.1, D13.3, J27.C2, U19.40
SIM_RST7: C131.1, D15.3, J31.C2, U22.40
SIM_RST8: C149.1, D17.3, J35.C2, U25.40
SIM_RST9: C167.1, D19.3, J39.C2, U28.40
VCCIO: C14.1, IC1.1, IC1.7, IC1.16, J3.3, Q1.1, R6.2, R8.1
VCCIO1: C29.1, IC2.1, IC2.7, IC2.16, J5.3, Q6.1, R9.1, R12.2
VCCIO2: C47.1, IC3.1, IC3.7, IC3.16, J9.3, Q9.1, R17.1, R20.2
VCCIO3: C65.1, IC4.1, IC4.7, IC4.16, J13.3, Q12.1, R25.1, R28.2
VCCIO4: C83.1, IC5.1, IC5.7, IC5.16, J17.3, Q15.1, R33.1, R36.2
VCCIO5: C101.1, IC6.1, IC6.7, IC6.16, J21.3, Q18.1, R41.1, R44.2
VCCIO6: C119.1, IC7.1, IC7.7, IC7.16, J25.3, Q21.1, R49.1, R52.2
VCCIO7: C137.1, IC8.1, IC8.7, IC8.16, J29.3, Q24.1, R57.1, R60.2
VCCIO8: C155.1, IC9.1, IC9.7, IC9.16, J33.3, Q27.1, R65.1, R68.2
VCCIO9: C173.1, IC10.1, IC10.7, IC10.16, J37.3, Q30.1, R73.1, R76.2
VOUT: C1.1, C2.2, J1.1, J3.1, U3.1
VOUT1: C32.1, C33.2, J5.1, J8.1, U6.1
VOUT2: C50.1, C51.2, J9.1, J12.1, U9.1
VOUT3: C68.1, C69.2, J13.1, J16.1, U12.1
VOUT4: C86.1, C87.2, J17.1, J20.1, U15.1
VOUT5: C104.1, C105.2, J21.1, J24.1, U18.1
VOUT6: C122.1, C123.2, J25.1, J28.1, U21.1
VOUT7: C140.1, C141.2, J29.1, J32.1, U24.1
VOUT8: C158.1, C159.2, J33.1, J36.1, U27.1
VOUT9: C176.1, C177.2, J37.1, J40.1, U30.1
VSIM: C5.2, C9.2, D2.1, J4.C1, U1.41
VSIM1: C26.2, C27.2, D3.1, J7.C1, U4.41
VSIM2: C44.2, C45.2, D5.1, J11.C1, U7.41
VSIM3: C62.2, C63.2, D7.1, J15.C1, U10.41
VSIM4: C80.2, C81.2, D9.1, J19.C1, U13.41
VSIM5: C98.2, C99.2, D11.1, J23.C1, U16.41
VSIM6: C116.2, C117.2, D13.1, J27.C1, U19.41
VSIM7: C134.2, C135.2, D15.1, J31.C1, U22.41
VSIM8: C152.2, C153.2, D17.1, J35.C1, U25.41
VSIM9: C170.2, C171.2, D19.1, J39.C1, U28.41

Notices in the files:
parts and their libraries:
SparkFun-Aesthetics: Licensing: Creative Commons ShareAlike 4.0 International - https://creativecommons.org/licenses/by-sa/4.0
